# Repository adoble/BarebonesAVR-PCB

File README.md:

# BarebonesAVR

A basic ATMega328P circuit that can be programmed with:
- an AVR programmer over a 6 pin ISP connection
- if the ATMega328P has an Arduino bootloader already loaded, then over an FTDI connection

The [KiCAD](http://kicad-pcb.org/) files are stored under [kicad](kicad).

## Circuit

The circuit is for a TQFB package (SMD).

## PCB Layout

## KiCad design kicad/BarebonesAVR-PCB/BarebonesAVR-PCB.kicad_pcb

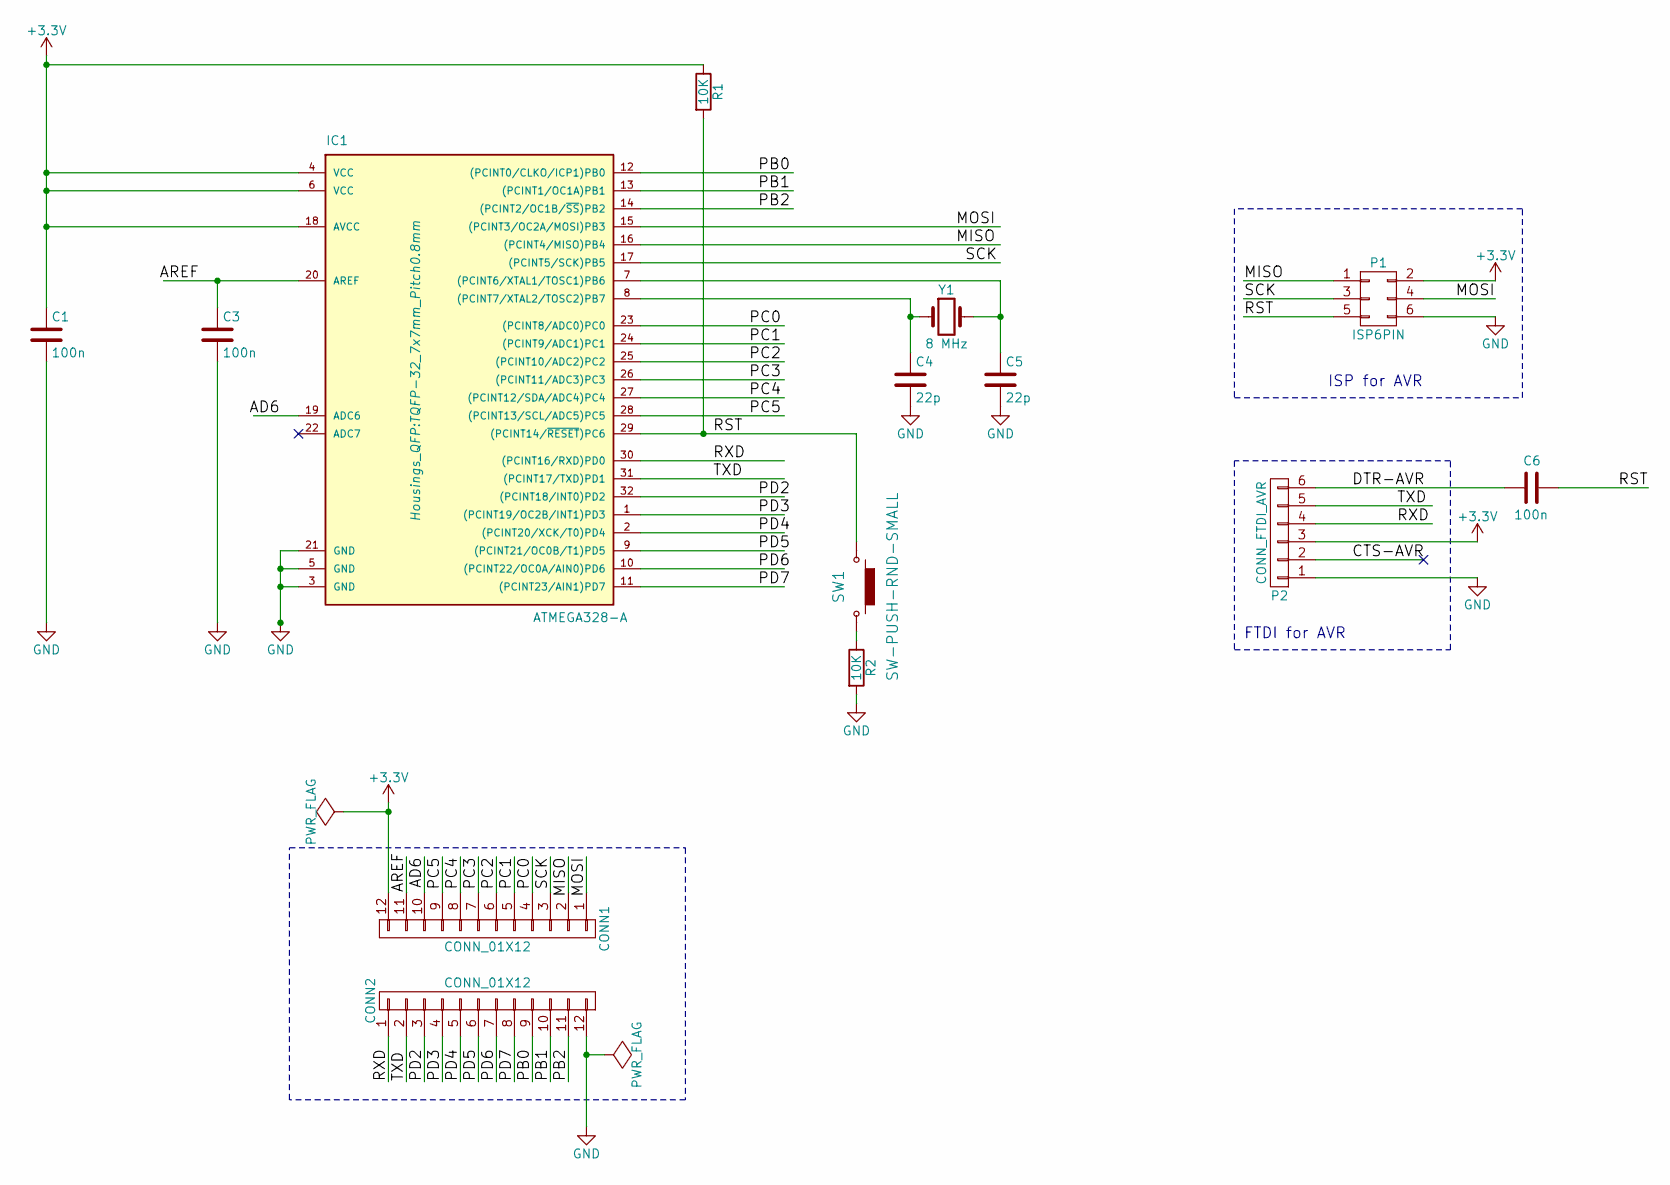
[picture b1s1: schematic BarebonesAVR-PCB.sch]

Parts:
C1, C3, C6: 100n; C_1812_HandSoldering
C4, C5: 22p; C_0805_HandSoldering
CONN1, CONN2: CONN_01X12; PINHEAD1-12
IC1: ATMEGA328-A; TQFP-32_7x7mm_Pitch0.8mm
P1: ISP6PIN; PINHEAD2-3
P2: CONN_FTDI_AVR; PINHEAD1-6
R1, R2: 10K; R_0805_HandSoldering
SW1: SW-PUSH-RND-SMALL
Y1: 8 MHz; Crystal_HC49-U_Vertical

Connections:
+3V3: C1.1, CONN1.12, IC1.4 (VCC), IC1.6 (VCC), IC1.18 (AVCC), P1.2, P2.3, R1.1
/AD6: CONN1.10, IC1.19 (ADC6)
/AREF: C3.1, CONN1.11, IC1.20 (AREF)
/CTS-AVR: P2.2
/DTR-AVR: C6.2, P2.6
/MISO: CONN1.2, IC1.16 ((PCINT4/MISO)PB4), P1.1
/MOSI: CONN1.1, IC1.15 ((PCINT3/OC2A/MOSI)PB3), P1.4
/PB0: CONN2.9, IC1.12 ((PCINT0/CLKO/ICP1)PB0)
/PB1: CONN2.10, IC1.13 ((PCINT1/OC1A)PB1)
/PB2: CONN2.11, IC1.14 ((PCINT2/OC1B/~SS~)PB2)
/PC0: CONN1.4, IC1.23 ((PCINT8/ADC0)PC0)
/PC1: CONN1.5, IC1.24 ((PCINT9/ADC1)PC1)
/PC2: CONN1.6, IC1.25 ((PCINT10/ADC2)PC2)
/PC3: CONN1.7, IC1.26 ((PCINT11/ADC3)PC3)
/PC4: CONN1.8, IC1.27 ((PCINT12/SDA/ADC4)PC4)
/PC5: CONN1.9, IC1.28 ((PCINT13/SCL/ADC5)PC5)
/PD2: CONN2.3, IC1.32 ((PCINT18/INT0)PD2)
/PD3: CONN2.4, IC1.1 ((PCINT19/OC2B/INT1)PD3)
/PD4: CONN2.5, IC1.2 ((PCINT20/XCK/T0)PD4)
/PD5: CONN2.6, IC1.9 ((PCINT21/OC0B/T1)PD5)
/PD6: CONN2.7, IC1.10 ((PCINT22/OC0A/AIN0)PD6)
/PD7: CONN2.8, IC1.11 ((PCINT23/AIN1)PD7)
/RST: C6.1, IC1.29 ((PCINT14/~RESET~)PC6), P1.5, R1.2, SW1.1
/RXD: CONN2.1, IC1.30 ((PCINT16/RXD)PD0), P2.4
/SCK: CONN1.3, IC1.17 ((PCINT5/SCK)PB5), P1.3
/TXD: CONN2.2, IC1.31 ((PCINT17/TXD)PD1), P2.5
GND: C1.2, C3.2, C4.2, C5.2, CONN2.12, IC1.3 (GND), IC1.5 (GND), IC1.21 (GND), P1.6, P2.1, R2.2
unnamed: C4.1, IC1.8 ((PCINT7/XTAL2/TOSC2)PB7), Y1.1
unnamed: C5.1, IC1.7 ((PCINT6/XTAL1/TOSC1)PB6), Y1.2
unnamed: R2.1, SW1.2

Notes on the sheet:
FTDI for AVR
ISP for AVR

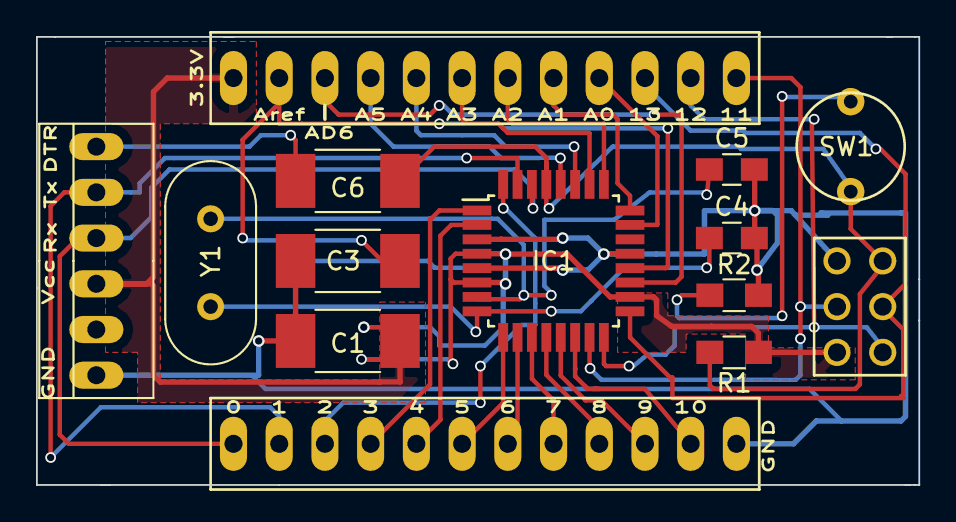
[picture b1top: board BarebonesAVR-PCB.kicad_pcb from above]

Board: 2 copper layers, 49.0 x 24.9 mm, 14 parts (0 on the bottom side), 29 nets.

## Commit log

2018-04-01 Added .gitignore file for KiCad projects
2018-04-01 New PCB layout
2018-04-01 Link problem
2018-04-01 Images correctly added
2018-04-02 Changed VCC lable to 3.3V
2018-06-16 R2 replaced by 0 ohm resistor
2018-06-16 Updated revision and date
